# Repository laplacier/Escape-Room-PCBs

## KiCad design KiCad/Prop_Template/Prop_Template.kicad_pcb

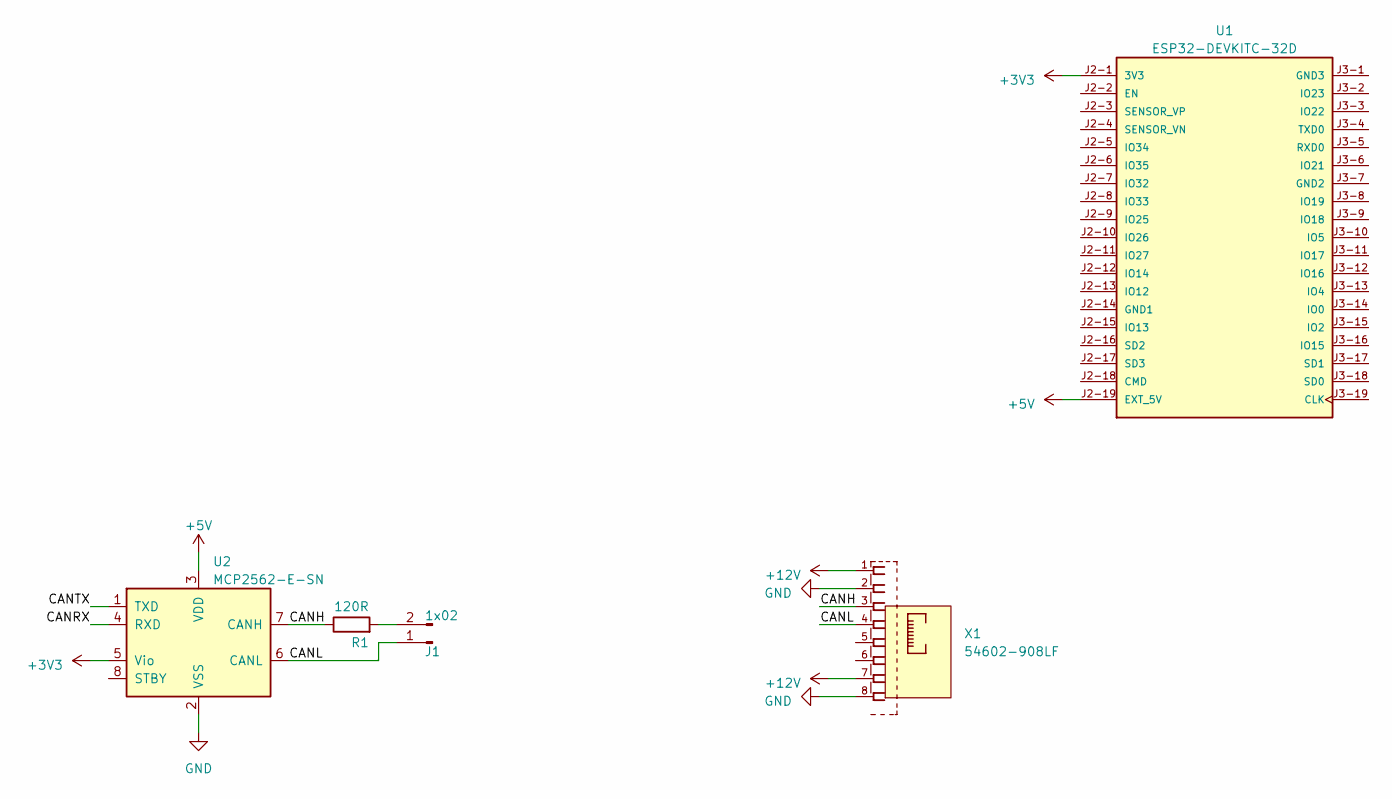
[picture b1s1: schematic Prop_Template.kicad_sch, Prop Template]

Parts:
J1: 1x02; PinHeader_1x02_P2.54mm_Vertical
R1: 120R; R_0603_1608Metric
U1: ESP32-DEVKITC-32D; MODULE_ESP32-DEVKITC-32D; PARTREV V4
U2: MCP2562-E-SN; SOIC-8_3.9x4.9mm_P1.27mm
X1: 54602-908LF; Digikey 609-1046-ND

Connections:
+3V3: U1.J2-1 (3V3), U2.5 (Vio)
+5V: U1.J2-19 (EXT_5V), U2.3 (VDD)
+12V: X1.1, X1.7
/CANH: R1.1, U2.7 (CANH), X1.3
/CANL: J1.1, U2.6 (CANL), X1.4
/CANRX: U2.4 (RXD)
/CANTX: U2.1 (TXD)
GND: U2.2 (VSS), X1.2, X1.8
unnamed: J1.2, R1.2

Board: 2 copper layers, 5 parts (0 on the bottom side), 7 nets, no tracks yet.

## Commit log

2022-10-06 Initial Commit
    Brainstorming additions. Added RJ45 for I2C and a relay for puzzle solution. Need to add DFMini Player, speakers, and voltage converter.
2022-10-06 Added all GPIO headers
    Placement seems good, but no space for the DFMini on the current layout. Board will have to exceed the footprint of the Mega, but need more additions to justify the space increase.
2022-10-18 Finished defining pin breakouts, wiring pins
2022-11-11 Changed DFMini TX/RX pins to compatible pins. Removed R1. Labeled 12V out terminal blocks.
2022-11-14 Added Buck Boost circuit
2022-12-01 Redesign to fix incorrect specs
    MOSFET needed to have a Vgs of 5V and all of the other passive components were adjusted to be more temperature/current compatible
2023-02-13 updated buck converter, added shift register boards
2023-02-13 Added pdf schematics to shift register boards
2023-02-14 Wire_Puzzle progress
2023-02-14 Progress, added audio amp, power
2023-02-15 Finished wire puzzle
2023-02-15 Cleaned up Wire_Puzzle PCB labels, added DC power jack
2023-04-26 Reorganized, started prop_template
    Trying to transition from EAGLE to KiCad for monetary purposes. Sorted schematics into program specific folders and began prop_template in KiCad.
2023-10-15 exported gerbers
